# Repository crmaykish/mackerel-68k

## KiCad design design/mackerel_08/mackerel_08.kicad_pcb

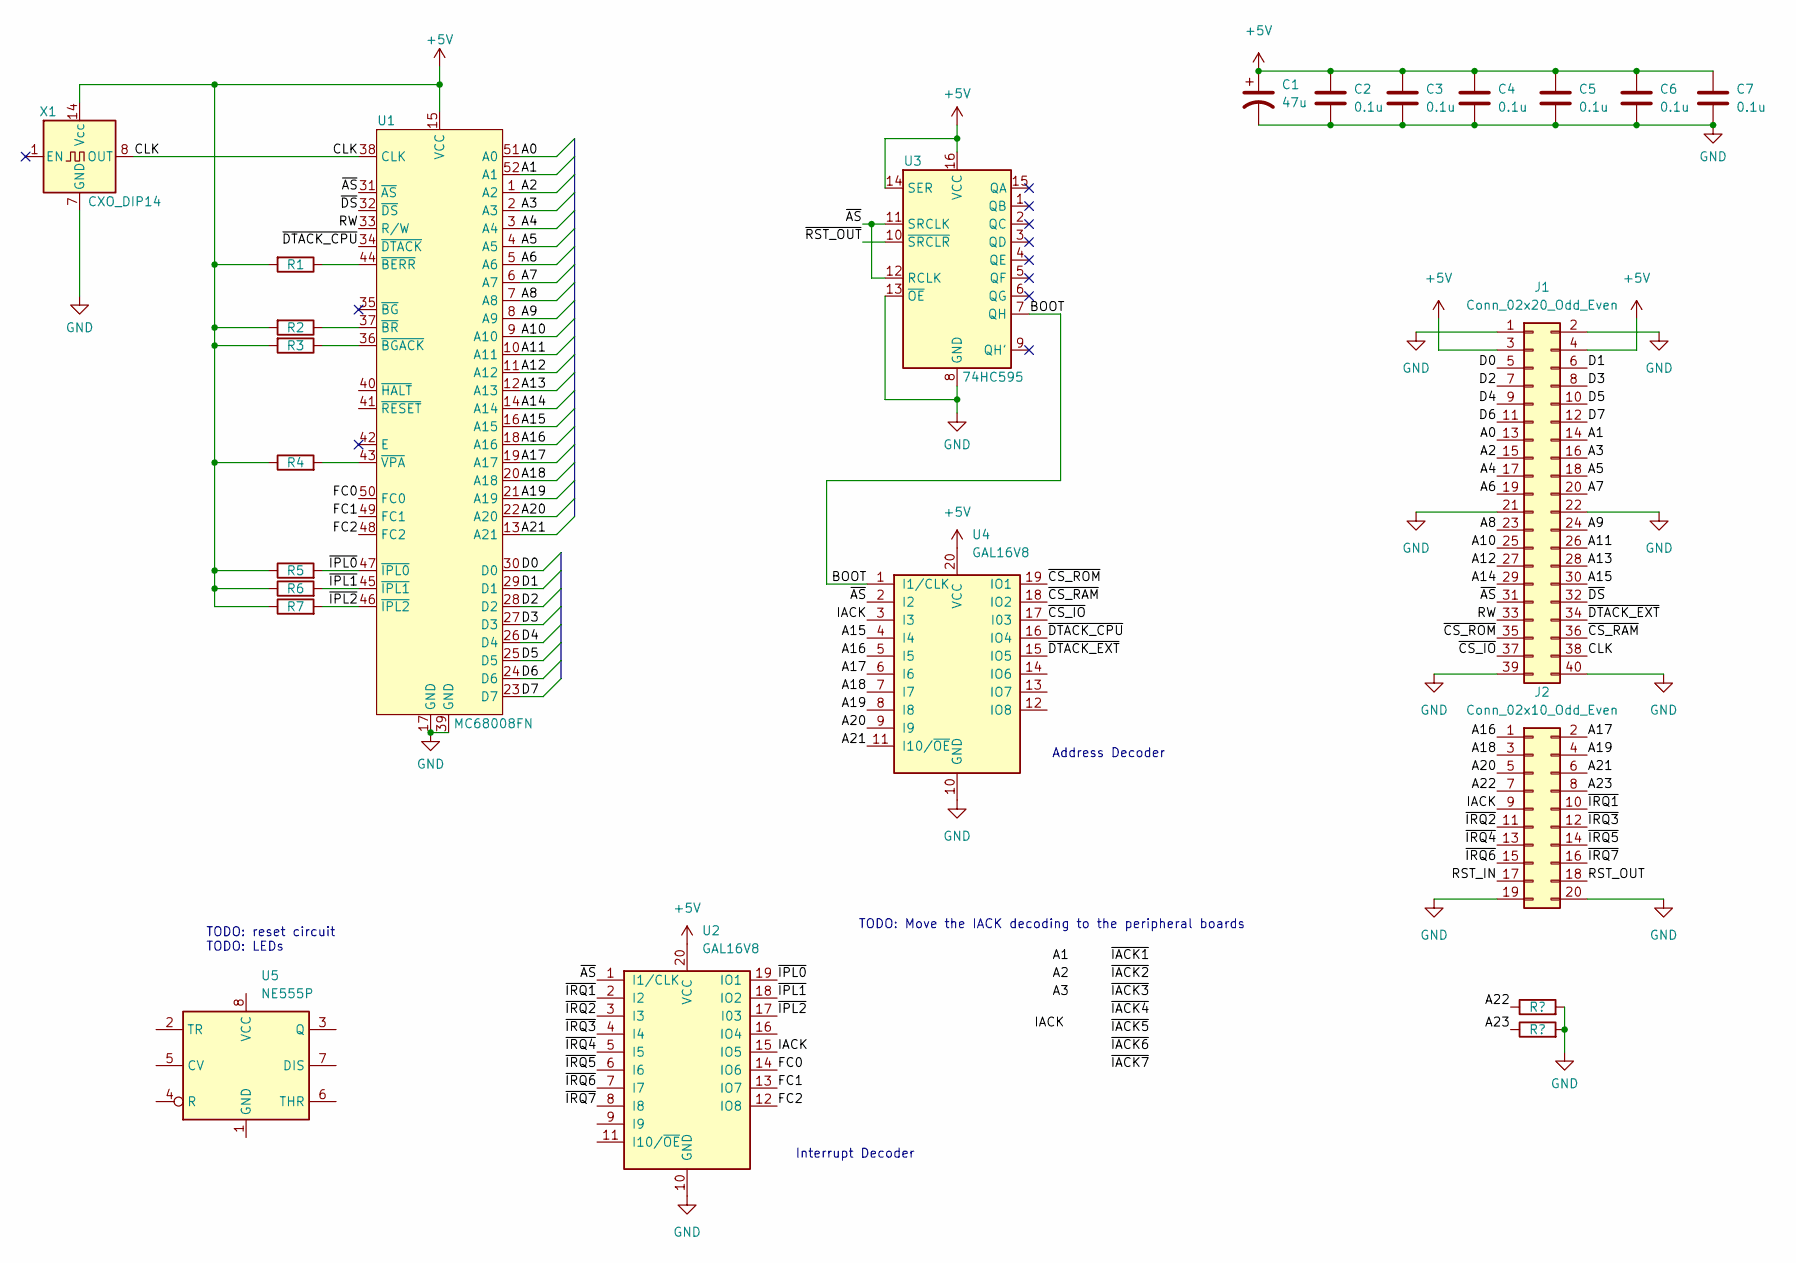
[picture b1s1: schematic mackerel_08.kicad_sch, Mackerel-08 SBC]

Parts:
C1: 47u; CP_Radial_D5.0mm_P2.50mm
C2, C3, C4, C5, C6, C7: 0.1u; C_Disc_D4.3mm_W1.9mm_P5.00mm
J1: Conn_02x20_Odd_Even; PinSocket_2x20_P2.54mm_Horizontal
J2: Conn_02x10_Odd_Even; PinSocket_2x10_P2.54mm_Horizontal
R1, R2, R3, R4, R5, R6, R7: 4k7; R_Axial_DIN0207_L6.3mm_D2.5mm_P10.16mm_Horizontal
U1: MC68008FN; PLCC-52_THT-Socket
U2, U4: GAL16V8; DIP-20_W7.62mm_Socket
U3: 74HC595; DIP-16_W7.62mm_Socket
U5: NE555P; DIP-8_W7.62mm_Socket
X1: CXO_DIP14; Oscillator_DIP-14

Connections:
+5V: C1.1, C2.1, C3.1, C4.1, C5.1, C6.1, C7.1, J1.3, J1.4, R1.2, R2.2, R3.2, R4.1, R5.1, R6.1, R7.1, U1.15 (VCC), U2.20 (VCC), U3.14 (SER), U3.16 (VCC), U4.20 (VCC), X1.14 (Vcc)
/A0: J1.13, U1.51 (A0)
/A1: J1.14, U1.52 (A1)
/A2: J1.15, U1.1 (A2)
/A3: J1.16, U1.2 (A3)
/A4: J1.17, U1.3 (A4)
/A5: J1.18, U1.4 (A5)
/A6: J1.19, U1.5 (A6)
/A7: J1.20, U1.6 (A7)
/A8: J1.23, U1.7 (A8)
/A9: J1.24, U1.8 (A9)
/A10: J1.25, U1.9 (A10)
/A11: J1.26, U1.10 (A11)
/A12: J1.27, U1.11 (A12)
/A13: J1.28, U1.12 (A13)
/A14: J1.29, U1.14 (A14)
/A15: J1.30, U1.16 (A15), U4.4 (I4)
/A16: J2.1, U1.18 (A16), U4.5 (I5)
/A17: J2.2, U1.19 (A17), U4.6 (I6)
/A18: J2.3, U1.20 (A18), U4.7 (I7)
/A19: J2.4, U1.21 (A19), U4.8 (I8)
/A20: J2.5, U1.22 (A20), U4.9 (I9)
/A21: J2.6, U1.13 (A21), U4.11 (I10/~OE)
/A22: J2.7
/A23: J2.8
/BOOT: U3.7 (QH), U4.1 (I1/CLK)
/CLK: J1.38, U1.38 (CLK), X1.8 (OUT)
/D0: J1.5, U1.30 (D0)
/D1: J1.6, U1.29 (D1)
/D2: J1.7, U1.28 (D2)
/D3: J1.8, U1.27 (D3)
/D4: J1.9, U1.26 (D4)
/D5: J1.10, U1.25 (D5)
/D6: J1.11, U1.24 (D6)
/D7: J1.12, U1.23 (D7)
/FC0: U1.50 (FC0), U2.14 (IO6)
/FC1: U1.49 (FC1), U2.13 (IO7)
/FC2: U1.48 (FC2), U2.12 (IO8)
/IACK: J2.9, U2.15 (IO5), U4.3 (I3)
/RST_IN: J2.17
/RST_OUT: J2.18
/RW: J1.33, U1.33 (R/W)
/~AS: J1.31, U1.31 (~AS), U2.1 (I1/CLK), U3.11 (SRCLK), U3.12 (RCLK), U4.2 (I2)
/~CS_IO: J1.37, U4.17 (I03)
/~CS_RAM: J1.36, U4.18 (IO2)
/~CS_ROM: J1.35, U4.19 (IO1)
/~DS: J1.32, U1.32 (~DS)
/~DTACK_CPU: U1.34 (~DTACK), U4.16 (IO4)
/~DTACK_EXT: J1.34, U4.15 (IO5)
/~IPL0: R5.2, U1.47 (~IPL0), U2.19 (IO1)
/~IPL1: R6.2, U1.45 (~IPL1), U2.18 (IO2)
/~IPL2: R7.2, U1.46 (~IPL2), U2.17 (I03)
/~IRQ1: J2.10, U2.2 (I2)
/~IRQ2: J2.11, U2.3 (I3)
/~IRQ3: J2.12, U2.4 (I4)
/~IRQ4: J2.13, U2.5 (I5)
/~IRQ5: J2.14, U2.6 (I6)
/~IRQ6: J2.15, U2.7 (I7)
/~IRQ7: J2.16, U2.8 (I8)
/~RST_OUT: U3.10 (~SRCLR)
GND: C1.2, C2.2, C3.2, C4.2, C5.2, C6.2, C7.2, J1.1, J1.2, J1.21, J1.22, J1.39, J1.40, J2.19, J2.20, U1.17 (GND), U1.39 (GND), U2.10 (GND), U3.8 (GND), U3.13 (~OE), U4.10 (GND), X1.7 (GND)
unnamed: R1.1, U1.44 (~BERR)
unnamed: R2.1, U1.37 (~BR)
unnamed: R3.1, U1.36 (~BGACK)
unnamed: R4.2, U1.43 (~VPA)

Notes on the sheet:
Address Decoder
Interrupt Decoder
TODO: reset circuit TODO: LEDs
TODO: Move the IACK decoding to the peripheral boards

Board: 2 copper layers, 22 parts (0 on the bottom side), 60 nets, no tracks yet.

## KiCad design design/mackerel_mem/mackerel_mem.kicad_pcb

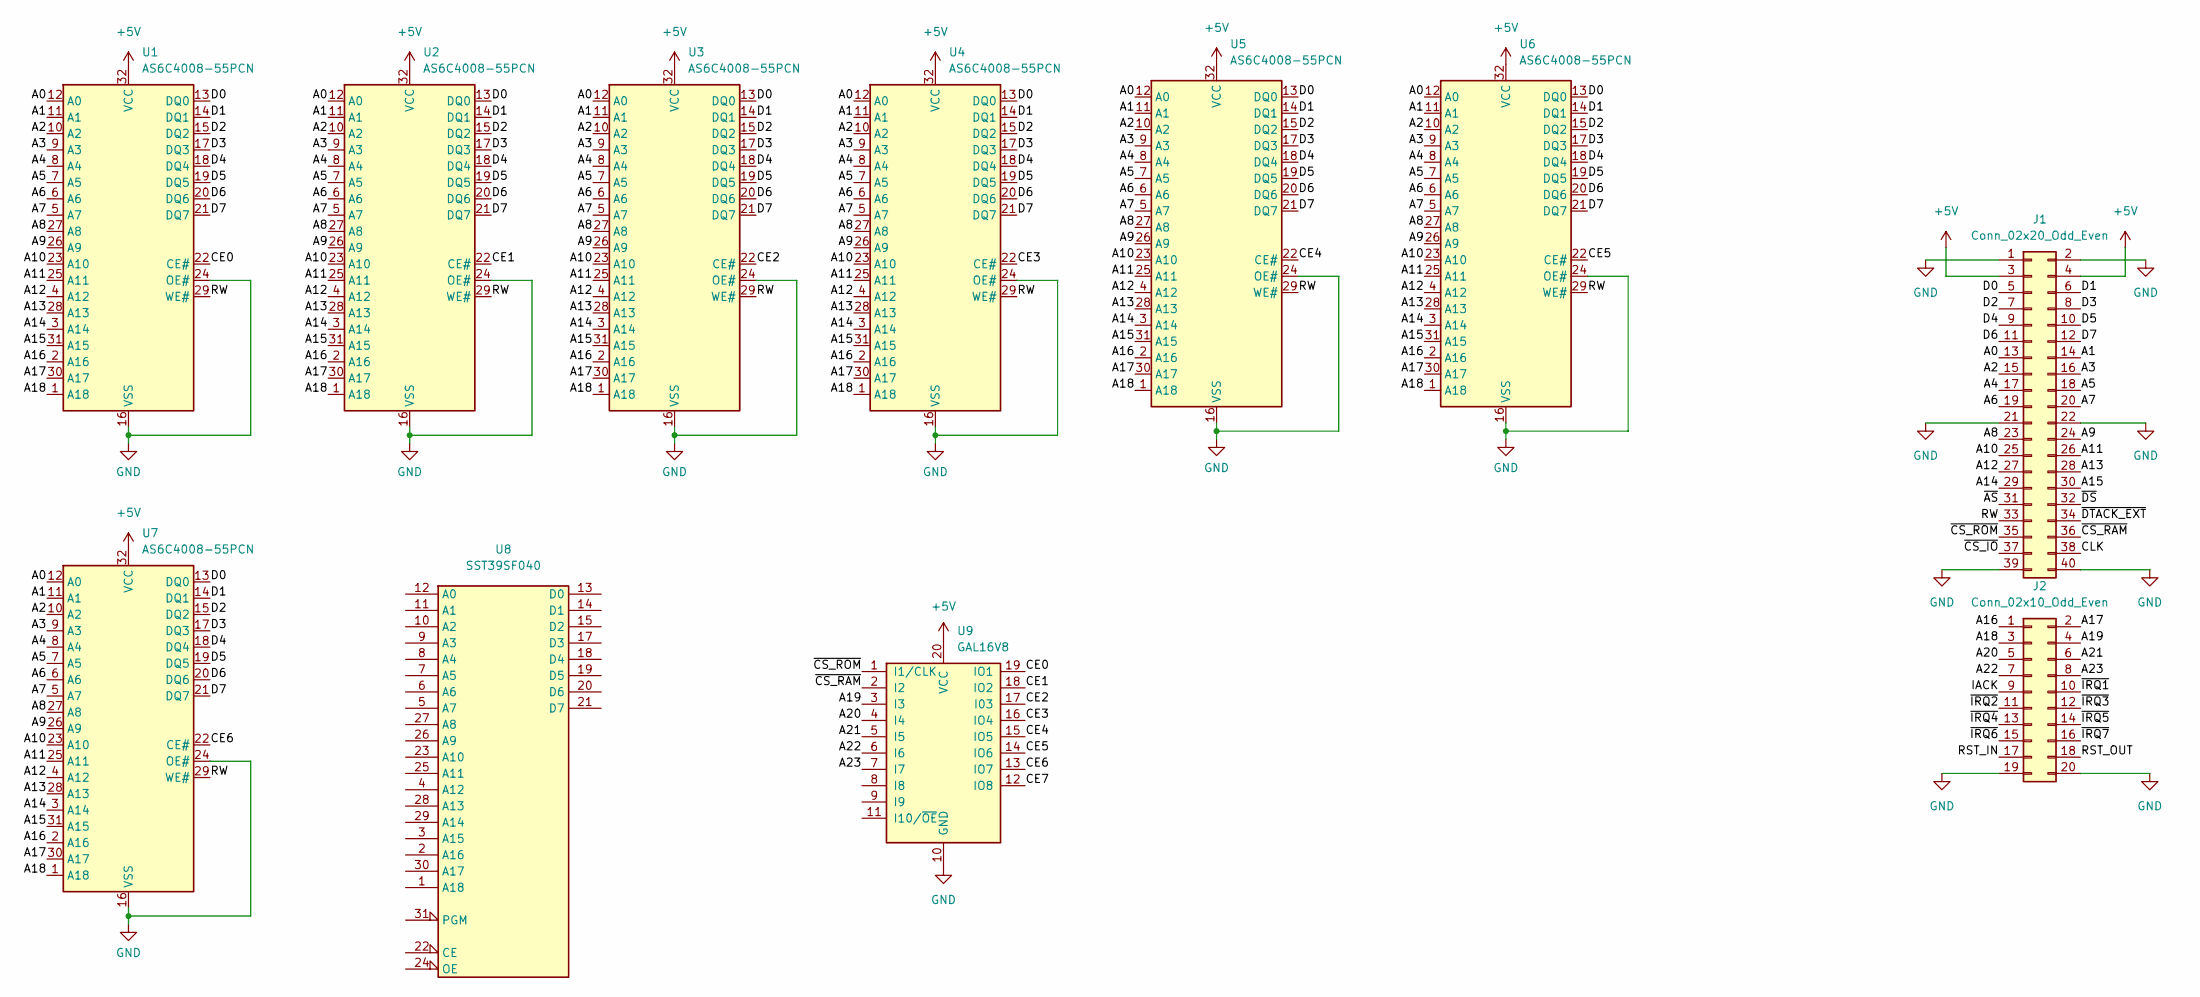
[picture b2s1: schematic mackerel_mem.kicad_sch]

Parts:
J1: Conn_02x20_Odd_Even; PinSocket_2x20_P2.54mm_Horizontal
J2: Conn_02x10_Odd_Even; PinSocket_2x10_P2.54mm_Horizontal
U1, U2, U3, U4, U5, U6, U7: AS6C4008-55PCN; DIP-32_W15.24mm_Socket
U8: SST39SF040; DIP-32_W15.24mm_Socket
U9: GAL16V8; DIP-20_W7.62mm_Socket

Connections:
+5V: J1.3, J1.4, U1.32 (VCC), U2.32 (VCC), U3.32 (VCC), U4.32 (VCC), U5.32 (VCC), U6.32 (VCC), U7.32 (VCC), U9.20 (VCC)
/A0: J1.13, U1.12 (A0), U2.12 (A0), U3.12 (A0), U4.12 (A0), U5.12 (A0), U6.12 (A0), U7.12 (A0)
/A1: J1.14, U1.11 (A1), U2.11 (A1), U3.11 (A1), U4.11 (A1), U5.11 (A1), U6.11 (A1), U7.11 (A1)
/A2: J1.15, U1.10 (A2), U2.10 (A2), U3.10 (A2), U4.10 (A2), U5.10 (A2), U6.10 (A2), U7.10 (A2)
/A3: J1.16, U1.9 (A3), U2.9 (A3), U3.9 (A3), U4.9 (A3), U5.9 (A3), U6.9 (A3), U7.9 (A3)
/A4: J1.17, U1.8 (A4), U2.8 (A4), U3.8 (A4), U4.8 (A4), U5.8 (A4), U6.8 (A4), U7.8 (A4)
/A5: J1.18, U1.7 (A5), U2.7 (A5), U3.7 (A5), U4.7 (A5), U5.7 (A5), U6.7 (A5), U7.7 (A5)
/A6: J1.19, U1.6 (A6), U2.6 (A6), U3.6 (A6), U4.6 (A6), U5.6 (A6), U6.6 (A6), U7.6 (A6)
/A7: J1.20, U1.5 (A7), U2.5 (A7), U3.5 (A7), U4.5 (A7), U5.5 (A7), U6.5 (A7), U7.5 (A7)
/A8: J1.23, U1.27 (A8), U2.27 (A8), U3.27 (A8), U4.27 (A8), U5.27 (A8), U6.27 (A8), U7.27 (A8)
/A9: J1.24, U1.26 (A9), U2.26 (A9), U3.26 (A9), U4.26 (A9), U5.26 (A9), U6.26 (A9), U7.26 (A9)
/A10: J1.25, U1.23 (A10), U2.23 (A10), U3.23 (A10), U4.23 (A10), U5.23 (A10), U6.23 (A10), U7.23 (A10)
/A11: J1.26, U1.25 (A11), U2.25 (A11), U3.25 (A11), U4.25 (A11), U5.25 (A11), U6.25 (A11), U7.25 (A11)
/A12: J1.27, U1.4 (A12), U2.4 (A12), U3.4 (A12), U4.4 (A12), U5.4 (A12), U6.4 (A12), U7.4 (A12)
/A13: J1.28, U1.28 (A13), U2.28 (A13), U3.28 (A13), U4.28 (A13), U5.28 (A13), U6.28 (A13), U7.28 (A13)
/A14: J1.29, U1.3 (A14), U2.3 (A14), U3.3 (A14), U4.3 (A14), U5.3 (A14), U6.3 (A14), U7.3 (A14)
/A15: J1.30, U1.31 (A15), U2.31 (A15), U3.31 (A15), U4.31 (A15), U5.31 (A15), U6.31 (A15), U7.31 (A15)
/A16: J2.1, U1.2 (A16), U2.2 (A16), U3.2 (A16), U4.2 (A16), U5.2 (A16), U6.2 (A16), U7.2 (A16)
/A17: J2.2, U1.30 (A17), U2.30 (A17), U3.30 (A17), U4.30 (A17), U5.30 (A17), U6.30 (A17), U7.30 (A17)
/A18: J2.3, U1.1 (A18), U2.1 (A18), U3.1 (A18), U4.1 (A18), U5.1 (A18), U6.1 (A18), U7.1 (A18)
/A19: J2.4, U9.3 (I3)
/A20: J2.5, U9.4 (I4)
/A21: J2.6, U9.5 (I5)
/A22: J2.7, U9.6 (I6)
/A23: J2.8, U9.7 (I7)
/CE0: U1.22 (CE#), U9.19 (IO1)
/CE1: U2.22 (CE#), U9.18 (IO2)
/CE2: U3.22 (CE#), U9.17 (I03)
/CE3: U4.22 (CE#), U9.16 (IO4)
/CE4: U5.22 (CE#), U9.15 (IO5)
/CE5: U6.22 (CE#), U9.14 (IO6)
/CE6: U7.22 (CE#), U9.13 (IO7)
/CE7: U9.12 (IO8)
/CLK: J1.38
/D0: J1.5, U1.13 (DQ0), U2.13 (DQ0), U3.13 (DQ0), U4.13 (DQ0), U5.13 (DQ0), U6.13 (DQ0), U7.13 (DQ0)
/D1: J1.6, U1.14 (DQ1), U2.14 (DQ1), U3.14 (DQ1), U4.14 (DQ1), U5.14 (DQ1), U6.14 (DQ1), U7.14 (DQ1)
/D2: J1.7, U1.15 (DQ2), U2.15 (DQ2), U3.15 (DQ2), U4.15 (DQ2), U5.15 (DQ2), U6.15 (DQ2), U7.15 (DQ2)
/D3: J1.8, U1.17 (DQ3), U2.17 (DQ3), U3.17 (DQ3), U4.17 (DQ3), U5.17 (DQ3), U6.17 (DQ3), U7.17 (DQ3)
/D4: J1.9, U1.18 (DQ4), U2.18 (DQ4), U3.18 (DQ4), U4.18 (DQ4), U5.18 (DQ4), U6.18 (DQ4), U7.18 (DQ4)
/D5: J1.10, U1.19 (DQ5), U2.19 (DQ5), U3.19 (DQ5), U4.19 (DQ5), U5.19 (DQ5), U6.19 (DQ5), U7.19 (DQ5)
/D6: J1.11, U1.20 (DQ6), U2.20 (DQ6), U3.20 (DQ6), U4.20 (DQ6), U5.20 (DQ6), U6.20 (DQ6), U7.20 (DQ6)
/D7: J1.12, U1.21 (DQ7), U2.21 (DQ7), U3.21 (DQ7), U4.21 (DQ7), U5.21 (DQ7), U6.21 (DQ7), U7.21 (DQ7)
/IACK: J2.9
/RST_IN: J2.17
/RST_OUT: J2.18
/RW: J1.33, U1.29 (WE#), U2.29 (WE#), U3.29 (WE#), U4.29 (WE#), U5.29 (WE#), U6.29 (WE#), U7.29 (WE#)
/~AS: J1.31
/~CS_IO: J1.37
/~CS_RAM: J1.36, U9.2 (I2)
/~CS_ROM: J1.35, U9.1 (I1/CLK)
/~DS: J1.32
/~DTACK_EXT: J1.34
/~IRQ1: J2.10
/~IRQ2: J2.11
/~IRQ3: J2.12
/~IRQ4: J2.13
/~IRQ5: J2.14
/~IRQ6: J2.15
/~IRQ7: J2.16
GND: J1.1, J1.2, J1.21, J1.22, J1.39, J1.40, J2.19, J2.20, U1.16 (VSS), U1.24 (OE#), U2.16 (VSS), U2.24 (OE#), U3.16 (VSS), U3.24 (OE#), U4.16 (VSS), U4.24 (OE#), U5.16 (VSS), U5.24 (OE#), U6.16 (VSS), U6.24 (OE#), U7.16 (VSS), U7.24 (OE#), U8.16 (GND), U9.10 (GND)
VCC: U8.32 (VCC)

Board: 2 copper layers, 11 parts (0 on the bottom side), 44 nets, no tracks yet.

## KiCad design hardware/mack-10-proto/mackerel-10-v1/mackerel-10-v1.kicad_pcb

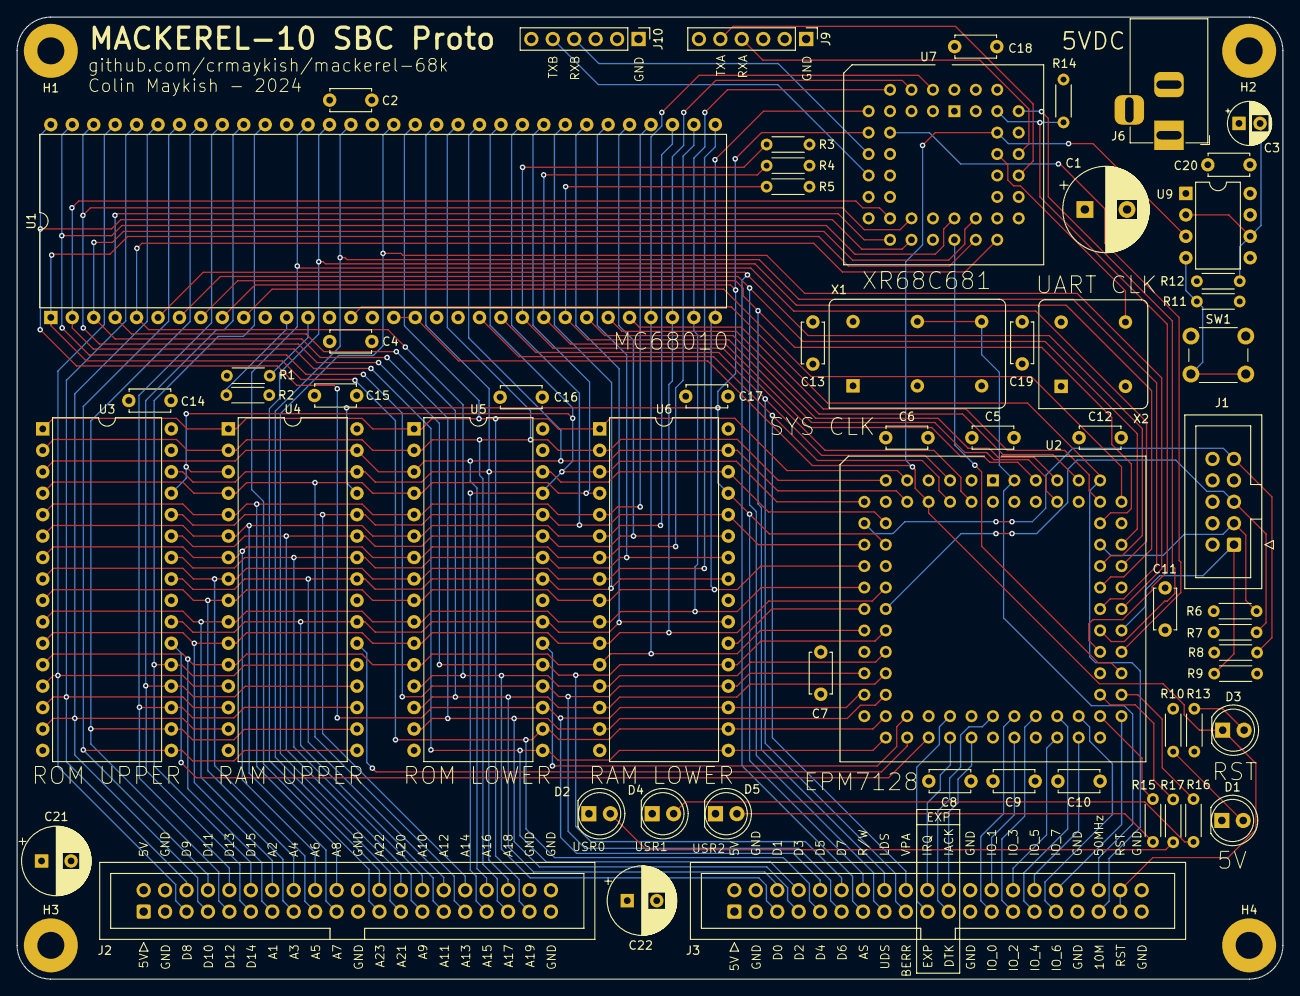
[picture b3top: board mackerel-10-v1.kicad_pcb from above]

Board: 4 copper layers, 150.0 x 114.0 mm, 65 parts (0 on the bottom side), 98 nets.

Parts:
C1: 1000uF; CP_Radial_D10.0mm_P5.00mm
C2, C4, C5, C6, C7, C8, C9, C10, C11, C12, C13, C14, C15, C16, C17, C18, C19, C20: 0.1uF; C_Disc_D4.7mm_W2.5mm_P5.00mm
C3: C_Polarized; CP_Radial_D5.0mm_P2.50mm
C21, C22: 1000uF; CP_Radial_D8.0mm_P3.50mm
D1, D2, D3, D4, D5: LED; LED_D5.0mm
H1, H2, H3, H4: MountingHole_Pad; MountingHole_3.2mm_M3_Pad
J1: Conn_02x05_Odd_Even; IDC-Header_2x05_P2.54mm_Vertical
J2, J3: Conn_02x20_Odd_Even; IDC-Header_2x20_P2.54mm_Vertical
J6: Barrel_Jack_MountingPin; BarrelJack_Horizontal
J9, J10: Conn_01x06; PinHeader_1x06_P2.54mm_Vertical
R1, R2, R3, R4, R5, R6, R7, R8, R9, R10, R11, R12, R13, R14, R15, R16, R17: R; R_Axial_DIN0204_L3.6mm_D1.6mm_P5.08mm_Horizontal
SW1: SW_Push; SW_PUSH_6mm_H5mm
U1: 68010D; DIP-64_W22.86mm
U2: PLCC-84_THT-Socket
U3, U5: SST39SF040; DIP-32_W15.24mm
U4, U6: AS6C4008-55PCN; DIP-32_W15.24mm
U7: XR68C681; PLCC-44_THT-Socket
U9: NE555P; DIP-8_W7.62mm
X1: 50MHz; Oscillator_DIP-14
X2: 3.6864MHz; Oscillator_DIP-8

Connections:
+5V: C1.1, C2.1, C3.1, C4.1, C5.1, C6.1, C7.1, C8.1, C9.1, C10.1, C11.1, C12.1, C13.1, C14.1, C15.1, C16.1, C17.1, C18.1, C19.1, C20.1, C21.1, C22.1, J1.4, J2.1, J2.2, J3.1, J3.2, J6.1, R1.1, R2.1, R3.1, R4.1, R5.1, R6.1, R7.1, R8.1, R10.1, R11.1, R13.1, R14.2, U1.14 (VCC), U1.49 (VCC), U2.3 (VCCINT), U2.13 (VCCIO), U2.26 (VCCIO), U2.38 (VCCIO), U2.43 (VCCINT), U2.53 (VCCIO), U2.66 (VCCIO), U2.78 (VCCIO), U3.31 (PGM), U3.32 (VCC), U4.32 (VCC), U5.31 (PGM), U5.32 (VCC), U6.32 (VCC), U7.44 (VCC), U9.8 (VCC), X1.14 (Vcc), X2.8 (Vcc)
A1: J2.13, U1.29 (A1), U2.24 (IO), U3.12 (A0), U4.12 (A0), U5.12 (A0), U6.12 (A0), U7.2 (A1)
A2: J2.14, U1.30 (A2), U2.21 (IO), U3.11 (A1), U4.11 (A1), U5.11 (A1), U6.11 (A1), U7.4 (A2)
A3: J2.15, U1.31 (A3), U2.20 (IO), U3.10 (A2), U4.10 (A2), U5.10 (A2), U6.10 (A2), U7.6 (A3)
A4: J2.16, U1.32 (A4), U2.18 (IO), U3.9 (A3), U4.9 (A3), U5.9 (A3), U6.9 (A3), U7.7 (A4)
A5: J2.17, U1.33 (A5), U3.8 (A4), U4.8 (A4), U5.8 (A4), U6.8 (A4)
A6: J2.18, U1.34 (A6), U3.7 (A5), U4.7 (A5), U5.7 (A5), U6.7 (A5)
A7: J2.19, U1.35 (A7), U3.6 (A6), U4.6 (A6), U5.6 (A6), U6.6 (A6)
A8: J2.20, U1.36 (A8), U3.5 (A7), U4.5 (A7), U5.5 (A7), U6.5 (A7)
A9: J2.27, U1.37 (A9), U3.27 (A8), U4.27 (A8), U5.27 (A8), U6.27 (A8)
A10: J2.28, U1.38 (A10), U3.26 (A9), U4.26 (A9), U5.26 (A9), U6.26 (A9)
A11: J2.29, U1.39 (A11), U3.23 (A10), U4.23 (A10), U5.23 (A10), U6.23 (A10)
A12: J2.30, U1.40 (A12), U3.25 (A11), U4.25 (A11), U5.25 (A11), U6.25 (A11)
A13: J2.31, U1.41 (A13), U3.4 (A12), U4.4 (A12), U5.4 (A12), U6.4 (A12)
A14: J2.32, U1.42 (A14), U2.16 (IO), U3.28 (A13), U4.28 (A13), U5.28 (A13), U6.28 (A13)
A15: J2.33, U1.43 (A15), U2.12 (IO), U3.29 (A14), U4.3 (A14), U5.29 (A14), U6.3 (A14)
A16: J2.34, U1.44 (A16), U2.10 (IO), U3.3 (A15), U4.31 (A15), U5.3 (A15), U6.31 (A15)
A17: J2.35, U1.45 (A17), U2.11 (IO), U3.2 (A16), U4.2 (A16), U5.2 (A16), U6.2 (A16)
A18: J2.36, U1.46 (A18), U2.15 (IO), U3.30 (A17), U4.30 (A17), U5.30 (A17), U6.30 (A17)
A19: J2.37, U1.47 (A19), U2.9 (IO), U3.1 (A18), U4.1 (A18), U5.1 (A18), U6.1 (A18)
A20: J2.26, U1.48 (A20), U2.64 (IO)
A21: J2.25, U1.50 (A21), U2.65 (IO)
A22: J2.24, U1.51 (A22), U2.67 (IO)
A23: J2.23, U1.52 (A23), U2.68 (IO)
CLK_CPU: J3.35, U1.15 (CLK), U2.75 (IO)
CLK_SRC: J3.36, U2.83 (GCLK1), X1.8 (OUT)
D0: J3.5, U1.5 (D0), U2.27 (IO), U5.13 (D0), U6.13 (DQ0), U7.28 (D0)
D1: J3.6, U1.4 (D1), U2.29 (IO), U5.14 (D1), U6.14 (DQ1), U7.18 (D1)
D2: J3.7, U1.3 (D2), U2.31 (IO), U5.15 (D2), U6.15 (DQ2), U7.27 (D2)
D3: J3.8, U1.2 (D3), U2.33 (IO), U5.17 (D3), U6.17 (DQ3), U7.19 (D3)
D4: J3.9, U1.1 (D4), U2.34 (IO), U5.18 (D4), U6.18 (DQ4), U7.26 (D4)
D5: J3.10, U1.64 (D5), U2.30 (IO), U5.19 (D5), U6.19 (DQ5), U7.20 (D5)
D6: J3.11, U1.63 (D6), U2.28 (IO), U5.20 (D6), U6.20 (DQ6), U7.25 (D6)
D7: J3.12, U1.62 (D7), U2.25 (IO), U5.21 (D7), U6.21 (DQ7), U7.21 (D7)
D8: J2.5, U1.61 (D8), U3.13 (D0), U4.13 (DQ0)
D9: J2.6, U1.60 (D9), U3.14 (D1), U4.14 (DQ1)
D10: J2.7, U1.59 (D10), U3.15 (D2), U4.15 (DQ2)
D11: J2.8, U1.58 (D11), U3.17 (D3), U4.17 (DQ3)
D12: J2.9, U1.57 (D12), U3.18 (D4), U4.18 (DQ4)
D13: J2.10, U1.56 (D13), U3.19 (D5), U4.19 (DQ5)
D14: J2.11, U1.55 (D14), U3.20 (D6), U4.20 (DQ6)
D15: J2.12, U1.54 (D15), U3.21 (D7), U4.21 (DQ7)
FC0: U1.28 (FC0), U2.76 (IO)
FC1: U1.27 (FC1), U2.77 (IO)
FC2: U1.26 (FC2), U2.79 (IO)
GND: C1.2, C2.2, C4.2, C5.2, C6.2, C7.2, C8.2, C9.2, C10.2, C11.2, C12.2, C13.2, C14.2, C15.2, C16.2, C17.2, C18.2, C19.2, C20.2, C21.2, C22.2, D1.1 (K), D2.1 (K), D4.1 (K), D5.1 (K), H1.1, H2.1, H3.1, H4.1, J1.2, J1.10, J2.3, J2.4, J2.21, J2.22, J2.38, J2.39, J2.40, J3.3, J3.4, J3.23, J3.24, J3.33, J3.34, J3.39, J3.40, J6.2, J9.1, J10.1, R9.2, R12.2, SW1.1, U1.16 (GND), U1.53 (GND), U2.1 (GCLRn), U2.2 (OE2/GCLK2), U2.7 (GND), U2.19 (GND), U2.32 (GND), U2.42 (GND), U2.47 (GND), U2.59 (GND), U2.72 (GND), U2.82 (GND), U2.84 (OE1), U3.16 (GND), U3.24 (OE), U4.16 (VSS), U4.24 (OE#), U5.16 (GND), U5.24 (OE), U6.16 (VSS), U6.24 (OE#), U7.3 (IP3), U7.5 (IP1), U7.8 (IP0), U7.22 (GND), U7.40 (IP2), U7.42 (IP5), U7.43 (IP4), U9.1 (GND), X1.7 (GND), X2.4 (GND)
GPIO_0: J3.25, U2.46 (IO)
GPIO_1: J3.26, U2.45 (IO)
GPIO_2: J3.27, U2.48 (IO)
GPIO_3: J3.28, U2.49 (IO)
GPIO_4: J3.29, U2.50 (IO)
GPIO_5: J3.30, U2.51 (IO)
GPIO_6: J3.31, U2.52 (IO)
GPIO_7: J3.32, U2.54 (IO)
unnamed: D1.2 (A), R10.2
unnamed: D3.2 (A), R13.2
unnamed: R15.1, U2.55 (IO)
unnamed: R16.1, U2.56 (IO)
unnamed: R17.1, U2.57 (IO)
unnamed: R2.2, U1.12 (BGACK)
unnamed: R1.2, U1.13 (BR)
unnamed: U7.36 (X1/CLK), X2.5 (OUT)
unnamed: R11.2, SW1.2, U9.4 (R)
unnamed: C3.2, R12.1, U9.2 (TR), U9.6 (THR)
RXA: J9.4, U7.35 (RXDA)
RXB: J10.4, U7.11 (RXDB)
R/W: J3.14, U1.9 (R/W), U2.17 (IO), U4.29 (WE#), U6.29 (WE#), U7.9 (/RW)
TCK: J1.1, R9.1, U2.62 (TCK)
TDI: J1.9, R8.2, U2.14 (TDI)
TDO: J1.3, R6.2, U2.71 (TDO)
TMS: J1.5, R7.2, U2.23 (TMS)
TXA: J9.5, U7.33 (TXDA)
TXB: J10.5, U7.13 (TXDB)
USR0: D5.2 (A), R15.2
USR1: D4.2 (A), R16.2
USR2: D2.2 (A), R17.2
/AS: J3.13, U1.6 (AS), U2.69 (IO)
/BERR: J3.17, U1.22 (BERR), U2.5 (IO)
/DTACK: U1.10 (DTACK), U2.74 (IO)
/DTACK_DUART: U2.60 (IO), U7.10 (/DTACK)
/DTACK_EXP: J3.21, U2.44 (IO)
/DUART: U2.63 (IO), U7.39 (CS)
/EXP: J3.19, U2.40 (IO)
/IACK_DUART: R14.1, U2.61 (IO), U7.41 (/IACK)
/IACK_EXP: J3.22, U2.41 (IO)
/IPL0: R5.2, U1.25 (IPL0), U2.80 (IO)
/IPL1: R4.2, U1.24 (IPL1), U2.81 (IO)
/IPL2: R3.2, U1.23 (IPL2), U2.4 (IO)
/IRQ_DUART: U2.58 (IO), U7.24 (INTR)
/IRQ_EXP: J3.20, U2.39 (IO)
/LDS: J3.16, U1.8 (LDS), U2.73 (IO)
/RESET: D3.1 (K), J3.37, J3.38, U1.17 (HALT), U1.18 (RESET), U2.8 (IO), U7.38 (/RESET), U9.3 (Q)
/ROM_LOWER: U2.36 (IO), U5.22 (CE)
/ROM_UPPER: U2.37 (IO), U3.22 (CE)
/SRAM_LOWER: U2.22 (IO), U6.22 (CE#)
/SRAM_UPPER: U2.35 (IO), U4.22 (CE#)
/UDS: J3.15, U1.7 (UDS), U2.70 (IO)
/VPA: J3.18, U1.21 (VPA), U2.6 (IO)
